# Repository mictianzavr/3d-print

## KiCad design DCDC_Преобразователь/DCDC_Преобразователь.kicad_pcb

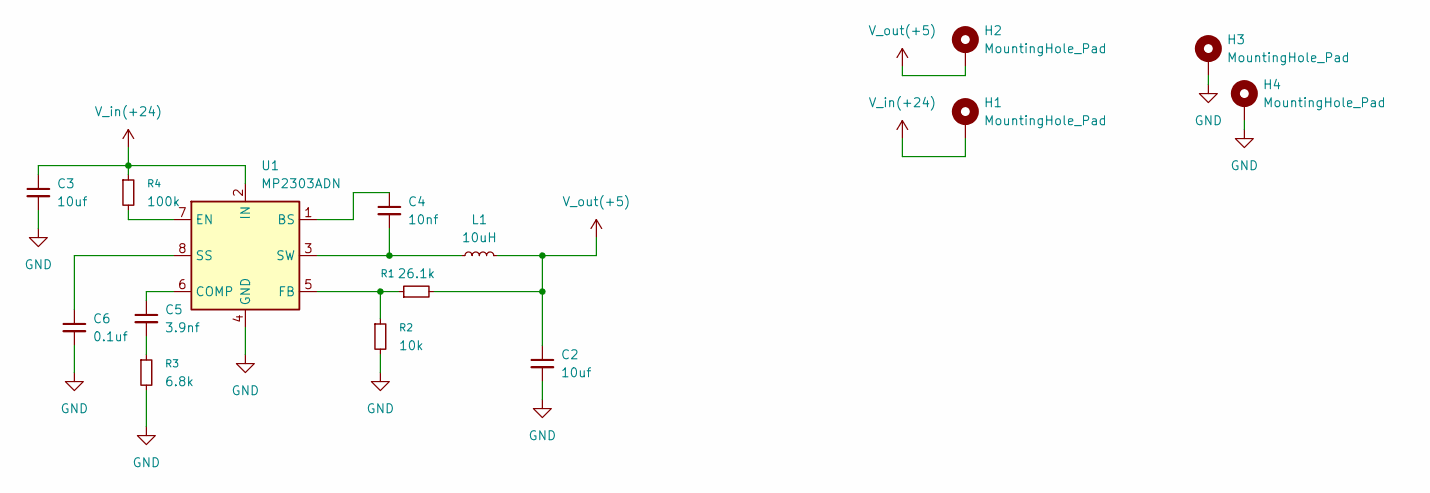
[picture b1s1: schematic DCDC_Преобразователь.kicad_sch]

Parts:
C2, C3: 10uf; C_0805_2012Metric
C4: 10nf; C_0805_2012Metric
C5: 3.9nf; C_0805_2012Metric
C6: 0.1uf; C_0805_2012Metric
H1, H2, H3, H4: MountingHole_Pad; MountingHole_2.7mm_M2.5_DIN965_Pad
L1: 10uH; L_APV_ANR5045
R1: 26.1k; R_0805_2012Metric
R2: 10k; R_0805_2012Metric
R3: 6.8k; R_0805_2012Metric
R4: 100k; R_0805_2012Metric
U1: MP2303ADN; SOIC-8-1EP_3.9x4.9mm_P1.27mm_EP2.62x3.51mm

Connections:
GND: C2.2, C3.2, C6.2, H3.1, H4.1, R2.2, R3.2, U1.4 (GND), U1.9
unnamed: C5.2, R3.1
unnamed: C4.1, U1.1 (BS)
unnamed: C5.1, U1.6 (COMP)
unnamed: R4.2, U1.7 (EN)
unnamed: R1.1, R2.1, U1.5 (FB)
unnamed: C6.1, U1.8 (SS)
unnamed: C4.2, L1.1, U1.3 (SW)
V_in(+24): C3.1, H1.1, R4.1, U1.2 (IN)
V_out(+5): C2.1, H2.1, L1.2, R1.2

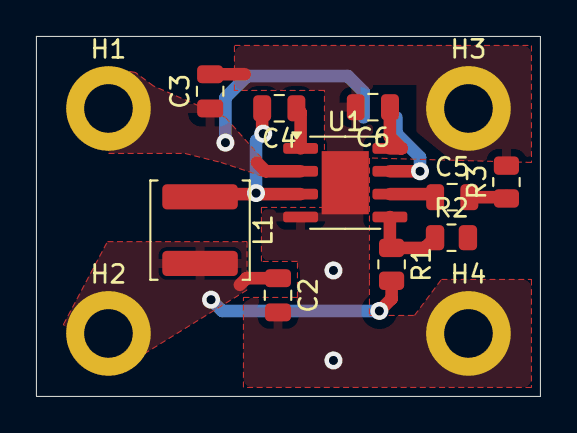
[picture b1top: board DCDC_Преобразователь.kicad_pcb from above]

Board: 2 copper layers, 28.0 x 20.0 mm, 15 parts (1 on the bottom side), 10 nets.
